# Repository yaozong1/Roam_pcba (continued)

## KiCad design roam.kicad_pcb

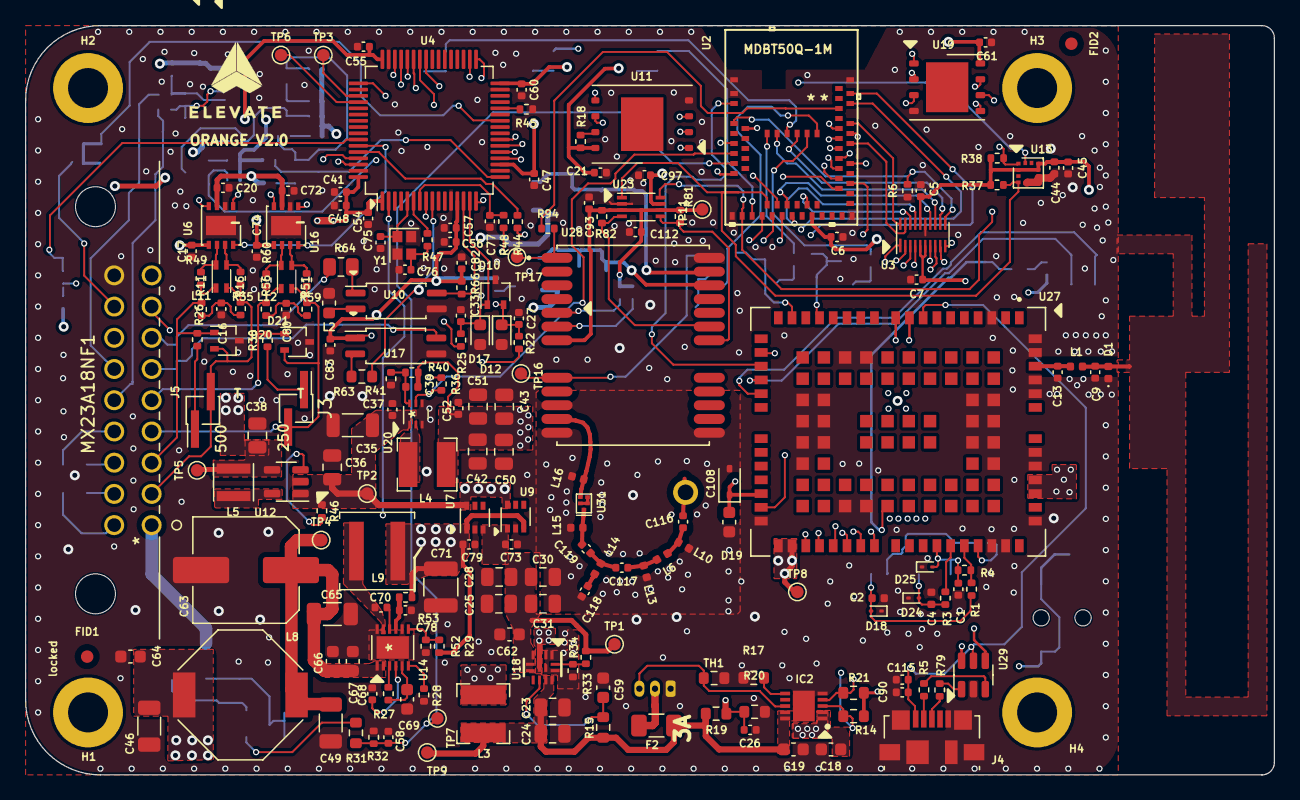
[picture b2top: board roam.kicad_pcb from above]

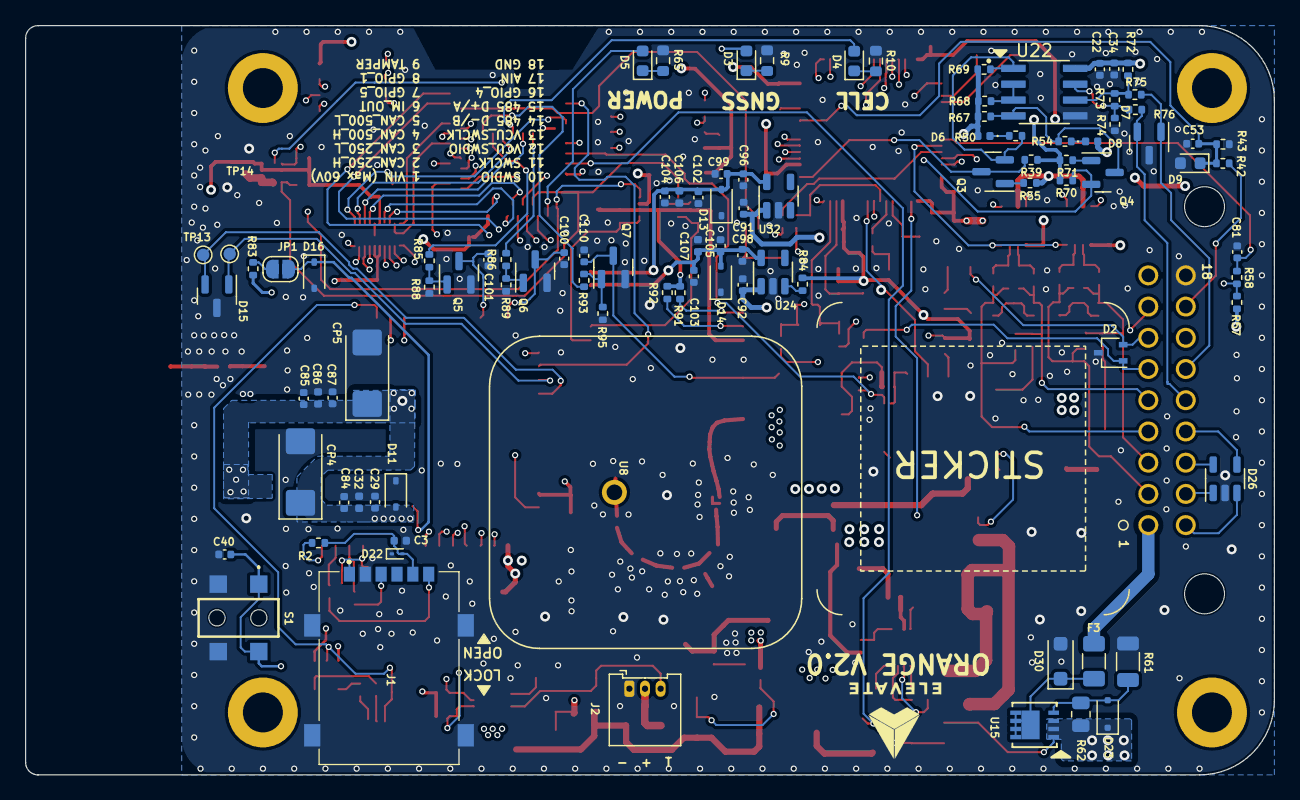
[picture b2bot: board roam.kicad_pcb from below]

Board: 6 copper layers, 100.0 x 60.0 mm, 301 parts (99 on the bottom side), 183 nets.

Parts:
C1, C5, C7, C17, C20, C21, C22, C26, C27, C29, C33, C37, C40, C44, C47, C48, C52, C53, C54, C55, C57, C58, C60, C61, C72, C73, C74, C77, C78, C79, C81, C82, C83, C85, C93, C97, C99, C104, C105, C110, C112, C115: 100nF; C_0402_1005Metric
C2, C3, C4, C32, C39, C86, C106, C107: 33pF; L_0402_1005Metric
C6, C41, C45, C102, C103: 10uF; C_0402_1005Metric
C9, C13: DNP; C_0402_1005Metric
C16, C80: 1nF; C_0402_1005Metric
C18, C19, C59, C62: 1uF; C_0603_1608Metric
C23, C24, C25, C28, C30, C31, C36, C38, C42, C43, C50, C51: 22uF; C_0805_2012Metric
C34, C56, C90, C96, C98: 1uF; C_0402_1005Metric
C35: 47uF; L_1206_3216Metric
C46, C49, C65: 4.7uF; C_1206_3216Metric
C63: 33uF; C_Elec_8x10.2
C64, C66: 0.1uF; C_0603_1608Metric
C67: 220pF; C_0603_1608Metric
C68: 12pF; C_0402_1005Metric
C69, C108: 2.2uF; C_0603_1608Metric
C70: 0.1uF; C_0402_1005Metric
C71: 22uF; C_1210_3225Metric
C75, C76, C84, C87: 10pF; C_0402_1005Metric
C91, C92: 2.2uF; C_0402_1005Metric
C100, C101: 10nF; C_0402_1005Metric
C116: 33nF; C_0402_1005Metric
C117, C118, C119: 4.7pF; C_0402_1005Metric
CP4, CP5: T520C107M010ATE025; CP_EIA-6032-28_Kemet-C
D1: AXGD10402; D_0402_1005Metric
D2, D10: BAT54AW; SOT-323_SC-70
D3, D4, D5: LED; LED_0603_1608Metric
D6, D8: LED; LED_0402_1005Metric
D7: PESD8V0L2BT-N; SOT-23
D9, D12, D17: 3v3; D_0603_1608Metric
D11, D13, D14: ESD56151W04; D_SOD-323
D15: PESD3V3L2BT; SOT-23
D16, D19: PESD3V3L1BA-N; D_SOD-323
D18, D22, D24, D25: ESD9C5.0ST5G; D_SOD-923
D20, D21: SM712_SOT23; SOT-323_SC-70
D23: MM3Z18VT1G; D_SOD-323F
D26: D5V0L4B5TS (5V); SOT-23-5
D30: SMF70CA (70V TVS); D_SOD-123F
F2: 3A; Fuse_1206_3216Metric
F3: 2A; Fuse_1206_3216Metric
FID1, FID2: Fiducial; Fiducial_1mm_Mask2mm
H1, H2, H3, H4: MountingHole; MountingHole_3.2mm_M3_DIN965_Pad
IC2: MCP73833T-FCI/MF; SON50P300X300X100-11N-D
J1: SIM8060-6-0-14-00-A; SIM8060601400A
J2: Battery; Molex_PicoBlade_53048-0310_1x03_P1.25mm_Horizontal
J3, J5: Conn_01x03_Pin; PinHeader_1x02_P1.27mm_Vertical_SMD_Pin1Left
J4: USB_B_Micro; USB_Micro-B_Molex_47346-0001
JP1: SolderJumper_2_Open; SolderJumper-2_P1.3mm_Open_RoundedPad1.0x1.5mm
L1, L6: 0nH; L_0402_1005Metric
L2: 2.2uH; L_0603_1608Metric
L3: 1.5uH; L_Bourns-SRN4018
L4: 2.2uH; L_Bourns-SRN4018
L5: 2.2uH; L_Taiyo-Yuden_MD-3030
L8: 10uH; L_Bourns-SRU1028_10.0x10.0mm
L9: 10uH; L_Coilcraft_XAL5030-XXX
L10, L13: DNP; L_0402_1005Metric
L11, L12: L_Ferrite_Coupled_1243; L_CommonModeChoke_Laird_CMA0805
L14: 9.1nH; L_0402_1005Metric
L15, L16: 5.1nH; L_0402_1005Metric
Q3, Q4: MMBT3904; SOT-23
Q5, Q6, Q7: BC846A,215; SOT-23
R1, R2, R3, R5, R35, R47, R49, R59, R60, R79, R94: 0; R_0402_1005Metric
R4: 15k; R_0402_1005Metric
R6, R42, R57: 100k; R_0402_1005Metric
R9, R10, R65: 750; R_0603_1608Metric
R11, R16, R51, R56: 2k8; R_0402_1005Metric
R14, R21: 4K7; R_0603_1608Metric
R15, R31: 300k; R_0603_1608Metric
R17: 2k; R_0603_1608Metric
R18, R46, R55, R58, R66, R71: 1k; R_0402_1005Metric
R19: 100k; R_0603_1608Metric
R20: 330k; R_0603_1608Metric
R22, R25: 2k; R_0402_1005Metric
R26, R30: 120; R_0402_1005Metric
R27, R32, R36, R39, R44, R45, R67, R68, R69, R70, R84: 10k; R_0402_1005Metric
R28, R73: DNP; R_0402_1005Metric
R29: 105k; R_0402_1005Metric
R33: 348k; R_0402_1005Metric
R34: 71.5k; R_0402_1005Metric
R37, R38, R72, R74, R85, R86, R93: 4K7; R_0402_1005Metric
R40: 169k; R_0402_1005Metric
R41: 30k; R_0402_1005Metric
R43: 3.3k; R_0402_1005Metric
R48: 100; R_0402_1005Metric
R50, R54: 5.1K; R_0402_1005Metric
R52: 23.2k; R_0402_1005Metric
R53: 4.7; R_0402_1005Metric
R61: 20k; R_1206_3216Metric
R62: 220k; R_0805_2012Metric
R63: 130; R_0603_1608Metric
R64: 680; R_0805_2012Metric
R75, R76: 10; R_0402_1005Metric
R81, R82: 2K2; R_0402_1005Metric
R83: 4k7; R_0402_1005Metric
R88, R89, R95: 47K; R_0402_1005Metric
R91, R92: 39k; R_0402_1005Metric
S1: ESE-11MV9; ESE11MV9
TCLOGO1, TCLOGO2: SYM_Magnet_Large; Logo-Text-Silk-Smaller
TCLOGO3: SYM_Magnet_Large; Sticker-frame
TCLOGO4: SYM_Magnet_Large; SIM-instruction
TH1: DNP; R_0603_1608Metric
TP1, TP2, TP4, TP5, TP8, TP11, TP16, TP17: TestPoint; TestPoint_Pad_D1.0mm
TP3: UART_TX; TestPoint_Pad_D1.0mm
TP6: UART_RX; TestPoint_Pad_D1.0mm
TP7: EBL; TestPoint_Pad_D1.0mm
TP9: T_BAT; TestPoint_Pad_D1.0mm
TP13: DBG_TX; TestPoint_Pad_D1.0mm
TP14: DBG_RXD; TestPoint_Pad_D1.0mm
U2: MDBT50Q-1M
U3: TXB0108DQSR; USON-20_2x4mm_P0.4mm
U4: STM32F105RBT6; LQFP-64_10x10mm_P0.5mm
U6, U16: MCP2562-E/MF; DFN-8-1EP_3x3mm_P0.65mm_EP1.55x2.4mm
U7, U9: LM66100DCKR; SOT-363_SC-70-6
U8: GP.1575.25.2.A.02
U10, U17: LTV-217; SOIC-4_4.55x2.6mm_P1.27mm
U11: W25N512GVEIG; WSON-8-1EP_8x6mm_P1.27mm_EP3.4x4.3mm
U12: LM3671MF-3.3/NOPB; SOT-23-5
U13: LIS2DH12TR; LIS12DH
U14: MAX17643ATC+; MAX17643ATCplus
U15: FDMC86139P; WDFN8-511DH-O_3p3x3p3x0p65_OSI
U18: MP3423GG; MP3423
U19: MX25R6435FZNIL0; WSON-8-1EP_6x5mm_P1.27mm_EP3.4x4mm
U20: TPS566242DRLR
U22: MAX13487EESAT; SOIC127P600X175-8N
U23: TXS0102DCU; VSSOP-8_2.3x2mm_P0.5mm
U24, U32: LP5907MFX-3.3; SOT-23-5
U27: EG915ULAAB-N05-SNNSA; XCVR_EG915ULAAB-N05-SNNSA
U28: LC29H; XCVR_LC29H
U29: USBLC6-2SC6; SOT-23-6
U31: B39162B8389P810; GNSS_Fliter 1.4x1.1mm
Y1: 25MHz; Crystal_SMD_2016-4Pin_2.0x1.6mm
locked: MX23A18NF1

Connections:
1V8: C7.1, C108.1, D19.1 (A1), R83.2, U3.5 (VCCA), U3.6 (OE), U27.29 (VDD_EXT)
2V8: C93.1, C112.2, R81.1, R82.1, R91.2, R92.2, TP11.1, U23.3 (VCCA), U23.6 (OE), U28.7 (VDD_EXT)
3V3_ALWAYS_ON: C5.1, C6.1, C17.2, C21.1, C38.1, C41.1, C44.1, C45.1, C47.2, C48.2, C54.2, C55.2, C56.1, C57.2, C60.2, C61.1, C74.2, C82.1, C83.1, C97.1, L5.2, R14.2, R18.1, R21.2, R36.1, R37.1, R38.1, R39.2, R57.2, R66.1, R70.2, R71.2, R84.2, TP5.1, U2.28 (VDD), U3.16 (VCCB), U4.1 (VBAT), U4.13 (VDDA), U4.19 (VDD), U4.32 (VDD), U4.48 (VDD), U4.64 (VDD), U6.5 (Vio), U11.8 (VCC), U12.4 (FB), U13.2 (CS), U13.9 (VDD), U13.10 (VDD_IO), U16.5 (Vio), U17.1, U19.8 (VCC), U23.7 (VCCB)
4V0: C29.1, C32.1, C39.1, C42.1, C43.1, C50.1, C51.1, C52.1, C84.2, C85.1, C86.1, C87.2, CP4.1, CP5.1, D11.2 (A2), L4.2, R40.1, TP8.1, U27.32 (VBAT_BB), U27.33 (VBAT_BB), U27.52 (VBAT_RF), U27.53 (VBAT_RF)
4V7_BOOST: C25.1, C28.1, C30.1, C31.1, C62.1, C73.1, R33.2, TP1.1, U7.3 (~CE), U9.1 (VIN), U18.4 (OUT), U18.5 (OUT), U18.6 (OUT)
5V0: C20.2, C22.1, C34.1, C35.1, C36.1, C37.1, C72.2, C91.1, C92.1, D6.2 (A), D8.2 (A), R46.1, R55.2, R67.2, R68.2, R69.2, R72.2, TP2.1, U6.3 (VDD), U7.6 (VOUT), U9.6 (VOUT), U12.1 (VIN), U16.3 (VDD), U20.1 (VIN), U22.8 (VCC), U24.1 (IN), U32.1 (IN)
5V0_BUCK: C18.1, C71.1, C79.1, IC2.1 (VDD_1), IC2.2 (VDD_2), L9.1, R29.1, R53.2, U7.1 (VIN), U9.3 (~CE)
60VIN: C49.1, C63.1, C65.1, C66.1, C67.1, L8.2, TP4.1, U14.1 (VIN), U14.2 (EN/UVLO)
+60V_IN: F3.1, locked.1
/100V_AIN: C53.1, D9.1 (K), R42.2, R43.1, U4.26 (PB0)
/3423_SW: L3.2, U18.3 (SW), U18.14 (SW)
/ACC_INT: U2.8 (P1.15), U13.12 (INT_1)
/AIN_100V: R42.1, locked.17
/AUX_LED: D5.2 (A), U2.17 (P0.00/XL1)
/CAN_250_H: D20.2 (A2), J5.2, L11.2, R16.1, R35.1, locked.2
/CAN_250_L: D20.1 (A1), L11.3, R11.2, R26.2, R49.1, locked.3
/CAN_500_H: D21.2 (A2), J3.2, L12.2, R51.1, R59.1, locked.4
/CAN_500_L: D21.1 (A1), L12.3, R30.2, R56.2, R60.1, locked.5
/CAN_SHDN: U4.59 (PB7), U6.8 (SHDN), U16.8 (SHDN)
/CHARGER_STAT_1: IC2.3 (STAT1), R14.1, U2.38 (P0.16)
/CHARGER_STAT_2: IC2.4 (STAT2), R21.1, U2.41 (P0.17)
/CONN_LED: D4.2 (A), U2.58 (P1.07)
/CTS_1V8: U3.4 (A4), U27.36 (MAIN_CTS)
/CTS_3V3: U2.24 (P0.08), U3.17 (B4)
/D+/A: D7.1 (A1), R75.1, locked.15
/D-/B: D7.2 (A2), R76.1, locked.14
/DCD_1V8: U3.7 (A5), U27.38 (MAIN_DCD)
/DCD_3V3: U2.23 (P0.07), U3.14 (B5)
/EBL: C58.1, R31.2, R32.1, TP7.1, U2.12 (P0.31/AIN7)
/EBL_60V: C46.1, C64.1, D23.1 (K), L8.1, R31.1, R62.1, U15.1 (S), U15.2 (S), U15.3 (S)
/FLASH_CS: U2.40 (P0.18/RST/QSPI-CSN), U19.1 (CS#)
/FLASH_MISO: U2.43 (P0.21/QSPI), U19.2 (SO/SIO1)
/FLASH_MISO2: U2.46 (P0.22/QSPI), U19.3 (WP#/SIO2)
/FLASH_MISO3: U2.45 (P0.23/QSPI), U19.7 (RST#/SIO3)
/FLASH_MOSI: U2.47 (P1.00/QSPI), U19.5 (SI/SIO0)
/FLASH_SCK: U2.42 (P0.19/QSPI-SCK), U19.6 (SCLK)
/GNSS_ANT: L16.2, U28.11 (RF_IN), U31.4 (OUT)
/GPIO15: R84.1, U24.3 (EN)
/GPIO_1: R22.1, locked.8
/GPIO_3V3_1: C27.1, D10.2, D12.1 (K), R22.2, U4.8 (PC0)
/GPIO_3V3_4: C33.1, D10.1, D17.1 (K), R25.2, U4.15 (PA1)
/GPIO_3V3_5: R66.2, U4.14 (PA0), U10.4
/GPIO_4: R25.1, locked.16
/GPIO_5: D2.2, R64.1, locked.7
/HSE_OSC_1: C75.1, U4.5 (PD0), Y1.1
/HSE_OSC_2: R47.1, U4.6 (PD1)
/IBL: C26.1, R19.2, R20.1, U2.14 (P0.30/AIN6)
/IM_OUT: D2.1, U17.4, locked.6
/IM_OUT_3V3: R63.1, U4.9 (PC1)
/LC29_RESET: C110.2, Q7.3 (C), TP16.1, U28.8 (~RESET)
/LC29_RESET_ESP32: R93.2, U2.61 (P1.01)
/LC29_WUP: R94.2, TP17.1, U28.1 (WAKEUP)
/LC29_WUP_ESP32: R94.1, U2.50 (P1.02)
/MODEM_DTR_1V8: U3.9 (A7), U27.30 (MAIN_DTR)
/MODEM_DTR_3V3: U2.59 (P1.05), U3.12 (B7)
/MODEM_RI_1V8: U3.8 (A6), U27.39 (MAIN_RI)
/MODEM_RI_3V3: U2.57 (P1.06), U3.13 (B6)
/MODEM_RX_1V8: U3.1 (A1), U27.34 (MAIN_RXD)
/MODEM_RX_3V3: U2.48 (P0.24), U3.20 (B1)
/MODEM_TX_1V8: U3.2 (A2), U27.35 (MAIN_TXD)
/MODEM_TX_3V3: U2.44 (P0.20), U3.19 (B2)
/NET_LED: U2.3 (P1.10), U27.21 (NET_STATUS)
/NRESET: R86.2, U2.56 (P1.04)
/NRF_LED: D3.2 (A), U2.5 (P1.12)
/NTC: IC2.8 (THERM), J2.3, TH1.1
/PWRKEY: R85.2, U2.60 (P1.03)
/RF_ANT: C13.1, L1.1, U27.60 (ANT_MAIN)
/RS485_RX: Q4.2 (E), R70.1, U4.16 (PA2)
/RS485_TX: Q3.3 (C), R39.1, U4.17 (PA3)
/RTS_1V8: U3.3 (A3), U27.37 (MAIN_RTS)
/RTS_3V3: U2.27 (P0.11), U3.18 (B3)
/SCL: R38.2, U2.16 (P0.27), U13.1 (SCL/SPC), U23.8 (B1)
/SCL_LC29: R82.2, U23.4 (A2), U28.19 (I2C_SCL)
/SDA: R37.2, U2.19 (P0.26), U13.4 (SDA/SDI/SDO), U23.1 (B2)
/SDA_LC29: R81.2, U23.5 (A1), U28.18 (I2C_SDA)
/SIM_CHIP_CLK: C3.1, D22.2 (A2), J1.C3 (CLK), R2.2
/SIM_CHIP_DATA: C2.1, D18.2 (A2), J1.C7 (I/O), R1.2
/SIM_CHIP_RST: C4.1, D24.2 (A2), J1.C2 (RST), R3.2
/SIM_CLK: R2.1, U27.46 (USIM1_CLK)
/SIM_DATA: R1.1, R4.1, U27.45 (USIM1_DATA)
/SIM_RST: R3.1, U27.44 (USIM1_RST)
/SIM_VDD: C1.1, D25.2 (A2), J1.C1 (VCC), R4.2, U27.43 (USIM1_VDD)
/STATUS_LED: U3.10 (A8), U27.20 (STATUS)
/STATUS_LED_3V3: R6.2, U2.4 (P1.11), U3.11 (B8)
/SWDCLK: D26.1 (K), U2.53 (SWDCLK), locked.11
/SWDIO: D26.3 (K), U2.51 (SWDIO), locked.10
/TAMPER_CONN: R57.1, R58.2, locked.9
/U20_EN: R36.2, U2.10 (P0.29/AIN5), U20.5 (EN)
/UART_RS485_RX_5V: Q4.3 (C), R54.2, R67.1, U22.4 (DI)
/UART_RS485_TX_5V: Q3.2 (E), R50.2, R69.1, U22.1 (RO)
/USB+: U27.9 (USB_DP), U29.6 (I/O1)
/USB-: U27.10 (USB_DM), U29.4 (I/O2)
/USB_DM: R5.2, U29.3 (I/O2)
/USB_DP: R79.2, U29.1 (I/O1)
/USB_VBUS: C90.1, C115.1, J4.1 (VBUS), U27.8 (USB_VBUS), U29.5 (VBUS)
/VCU_BOOT0: R44.2, U2.36 (P0.14)
/VCU_CAN1_RX: U4.61 (PB8), U16.4 (RXD)
/VCU_CAN1_TX: U4.62 (PB9), U16.1 (TXD)
/VCU_CAN2_RX: U4.33 (PB12), U6.4 (RXD)
/VCU_CAN2_TX: U4.34 (PB13), U6.1 (TXD)
/VCU_FLASH_CS: U4.20 (PA4), U11.1 (CS#)
/VCU_FLASH_MISO: U4.22 (PA6), U11.2 (SO/SIO1)
/VCU_FLASH_MOSI: U4.23 (PA7), U11.5 (SI/SIO0)
/VCU_FLASH_SCK: U4.21 (PA5), U11.6 (SCLK)
/VCU_FLASH_WP: U4.41 (PA8), U11.3 (WP#/SIO2)
/VCU_NRST: R48.2, U2.37 (P0.13)
/VCU_SWCLK: D26.4 (K), U4.49 (PA14), locked.13
/VCU_SWDIO: D26.5 (K), U4.46 (PA13), locked.12
/VCU_TAMP: C40.1, S1.1 (NO_1), S1.2 (NO_2), U4.2 (PC13)
/VCU_TAMPER_CONN: C81.1, R58.1, U4.58 (PB6)
/VCU_USART2_CTS: U2.20 (P0.04/AIN2), U4.44 (PA11)
/VCU_USART2_RTS: U2.18 (P0.01/XL2), U4.45 (PA12)
/VCU_USART2_RX: U2.21 (P0.05/AIN3), U4.43 (PA10)
/VCU_USART2_TX: U2.22 (P0.06), U4.42 (PA9)
/usb_boot: D16.1 (A1), JP1.1 (A), U27.75 (USB_BOOT)
GND: C1.2, C2.2, C3.2, C4.2, C5.2, C6.2, C7.2, C9.1, C9.2, C13.2, C16.2, C17.1, C18.2, C19.2, C20.1, C21.2, C22.2, C23.2, C24.2, C25.2, C26.2, C27.2, C28.2, C29.2, C30.2, C31.2, C32.2, C33.2, C34.2, C35.2, C36.2, C37.2, C38.2, C40.2, C41.2, C42.2, C43.2, C44.2, C45.2, C46.2, C47.1, C48.1, C49.2, C50.2, C51.2, C52.2, C53.2, C54.1, C55.1, C56.2, C57.1, C58.2, C59.2, C60.1, C61.2, C62.2, C63.2, C64.2, C65.2, C66.2, C67.2, C68.2, C69.2, C71.2, C72.1, C73.2, C74.1, C75.2, C76.2, C77.1, C78.2, C79.2, C80.2, C81.2, C82.2, C83.2, C84.1, C85.2, C86.2, C87.1, C90.2, C91.2, C92.2, C93.2, C96.2, C97.2, C98.2, C99.2, C100.1, C101.1, C102.2, C103.2, C104.1, C105.1, C106.2, C107.2, C108.2, C110.1, C112.1, C115.2, C118.1, CP4.2, CP5.2, D1.1 (A1), D1.2 (A2), D2.3, D7.3 (A3), D9.2 (A), D10.3, D11.1 (A1), D12.2 (A), D13.1 (A1), D14.1 (A1), D15.3 (common), D16.2 (A2), D17.2 (A), D18.1 (A1), D19.2 (A2), D20.3 (common), D21.3 (common), D22.1 (A1), D24.1 (A1), D25.1 (A1), D26.2 (A), D30.2 (A2), IC2.5 (VSS), IC2.11 (EP), J1.C5 (GND_1), J1.G1 (GND_2), J1.G2 (GND_3), J1.G3 (GND_4), J1.G4 (GND_5), J2.1, J4.5 (GND), J4.6 (Shield), L1.2, L2.2, L10.1, L13.1, L15.1, L16.1, Q5.2 (E), Q6.2 (E), Q7.2 (E), R6.1, R9.1, R10.1, R17.2, R20.2, R28.1, R32.2, R34.1, R41.2, R43.2, R45.1, R52.2, R61.2, R65.1, R74.1, R88.1, R89.1, R95.1, S1.C1 (COM_1), S1.C2 (COM_2), TH1.2, U2.1 (GND), U2.2 (GND), U2.15 (GND), U2.33 (GND), U2.55 (GND), U3.15 (GND), U4.12 (VSSA), U4.18 (VSS), U4.31 (VSS), U4.47 (VSS), U4.63 (VSS), U6.2 (VSS), U6.9 (PAD), U7.2 (GND), U9.2 (GND), U10.3, U11.4 (GND), U12.2 (GND), U13.5 (RES), U13.6 (GND), U13.7 (GND), U13.8 (GND), U14.8 (GND), U14.12 (PGND), U14.13 (EPAD), U16.2 (VSS), U16.9 (PAD), U17.3, U18.1 (PGND), U18.2 (PGND), U18.11 (AGND), U18.13 (PGND), U19.4 (GND), U20.3 (AGND), U20.4 (GND), U22.5 (GND), U23.2 (GND), U24.2 (GND), U27.3 (GND), U27.31 (GND), U27.47 (USIM1_GND), U27.48 (GND), U27.50 (GND), U27.54 (GND), U27.55 (GND), U27.58 (GND), U27.59 (GND), U27.61 (GND), U27.62 (GND), U27.67 (GND), U27.68 (GND), U27.69 (GND), U27.70 (GND), U27.71 (GND), U27.72 (GND), U27.73 (GND), U27.74 (GND), U27.79 (GND), U27.80 (GND), U27.81 (GND), U27.82 (GND), U27.89 (GND), U27.90 (GND), U27.91 (GND), U27.100 (GND), U27.101 (GND), U27.102 (GND), U28.10 (GND), U28.12 (GND), U28.13 (GND), U28.24 (GND), U29.2 (GND), U31.2 (GND), U31.3 (GND), U31.5 (GND), U32.2 (GND), Y1.2, Y1.4, locked.18
unnamed: C16.1, R11.1, R16.2
unnamed: C76.1, R47.2, Y1.3
unnamed: C80.1, R51.2, R56.1
unnamed: C116.1, L6.1, L10.2
unnamed: C116.2, U8.1
unnamed: C117.1, L6.2, L13.2
unnamed: C117.2, C119.1, L14.2
unnamed: C118.2, L14.1
unnamed: D3.1 (K), R9.2
unnamed: D4.1 (K), R10.2
unnamed: D5.1 (K), R65.2
unnamed: D6.1 (K), R50.1
unnamed: D8.1 (K), R54.1
unnamed: D15.1 (A1), TP14.1, U27.22 (DBG_RXD)
unnamed: D15.2 (A2), TP13.1, U27.23 (DBG_TXD)
unnamed: D23.2 (A), R61.1, R62.2, U15.4 (G)
unnamed: D30.1 (A1), F3.2, U15.5 (D), U15.6 (D), U15.7 (D), U15.8 (D)
unnamed: IC2.6 (PROG), R17.1
unnamed: F2.2, J2.2
unnamed: J3.1, R30.1
unnamed: J4.3 (D+), R79.1
unnamed: J4.2 (D-), R5.1
unnamed: J5.1, R26.1
unnamed: JP1.2 (B), R83.1
unnamed: L2.1, U10.2
unnamed: Q3.1 (B), R55.1
unnamed: Q4.1 (B), R71.1
unnamed: Q5.1 (B), R85.1, R88.2
unnamed: C101.2, Q5.3 (C), U27.15 (PWRKEY)
unnamed: Q6.1 (B), R86.1, R89.2
unnamed: C100.2, Q6.3 (C), U27.17 (~RESET)
unnamed: Q7.1 (B), R93.1, R95.2
unnamed: R63.2, U17.2
unnamed: R64.2, U10.1
unnamed: R44.1, U4.60 (BOOT0)
unnamed: C77.2, R48.1, U4.7 (NRST)
unnamed: R45.2, U4.28 (PB2)
unnamed: TP3.1, U4.51 (PC10)
unnamed: TP6.1, U4.52 (PC11)
unnamed: L11.1, R35.2, U6.7 (CANH)
unnamed: L11.4, R49.2, U6.6 (CANL)
unnamed: R18.2, U11.7 (RST#/SIO3)
unnamed: R46.2, U12.3 (EN)
unnamed: L5.1, U12.5 (SW)
unnamed: R27.2, U14.3 (*RESET)
unnamed: C70.2, U14.10 (BST)
unnamed: C78.1, R53.1, U14.9 (EXTVCC)
unnamed: R29.2, R52.1, U14.7 (FB)
unnamed: C70.1, L9.2, U14.11 (LX)
unnamed: R28.2, U14.6 (RT/SYNC)
unnamed: C68.1, U14.4 (SS)
unnamed: C69.1, R27.1, U14.5 (VCC)
unnamed: L12.1, R59.2, U16.7 (CANH)
unnamed: L12.4, R60.2, U16.6 (CANL)
unnamed: C59.1, R15.2, U18.8 (EN)
unnamed: R33.1, R34.2, U18.12 (FB)
unnamed: C39.2, R40.2, R41.1, U20.6 (FB)
unnamed: L4.1, U20.2 (SW)
unnamed: R72.1, R73.2, R75.2, U22.6 (A)
unnamed: R73.1, R74.2, R76.2, U22.7 (B)
unnamed: R68.1, U22.2 (~RE), U22.3 (~SHDN)
unnamed: R91.1, U28.5 (D_SEL1)
unnamed: R92.1, U28.6 (D_SEL2)
unnamed: C119.2, L15.2, U31.1 (IN)
VBAT: C19.1, C23.1, C24.1, F2.1, IC2.9 (VBAT_1), IC2.10 (VBAT_2), L3.1, R15.1, R19.1, TP9.1, U18.9 (IN), U18.10 (INA)
VCC_LC29: C96.1, C99.1, C102.1, C104.2, C106.1, D13.2 (A2), U28.23 (VCC), U32.5 (OUT)
V_BCKP_LC29: C98.1, C103.1, C105.2, C107.1, D14.2 (A2), U24.5 (OUT), U28.22 (V_BCKP)

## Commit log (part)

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2022-12-15 add README
2022-12-15 Init
2022-12-15 Placed sketch components
2022-12-20 Reduced component count
2022-12-21 Updated smaller footprint
2022-12-26 Worked on connector
2022-12-28 Draw 95V
2022-12-28 added 3d models for missing parts
2022-12-29 Added DC booster
2022-12-29 new dc booster
2022-12-29 Save
2022-12-30 Routing
2023-01-02 Routed
2023-01-02 Component selection in progress
2023-01-05 Added Digi-key PN to all components
2023-01-23 phase 2 start
2023-01-26 single shield on vin dcdc
2023-01-31 updated layout, not done
2023-01-31 Done, execpt ERC
2023-02-01 ready for production
2023-02-01 changed tvs diodes and added missing cupper fill
2023-02-02 gerber sent to production
2023-02-08 gsm antenna template
2023-02-09 tc-kicad-comp folder
2023-02-15 new rounting 2/15
2023-02-17 before updating to kicad7
2023-02-19 KICAD 7
2023-02-21 P3_ ready to print
2023-02-21 fix silkscreen
2023-02-21 Added all 3d models
2023-02-22 Fixed In1 and In2 Sequence
2023-02-23 started to implement the changelog for phase 3
2023-03-08 new 5V dcdc
2023-03-09 save before mayhem
2023-03-09 unboken gnd plane + cleared space around the LNA
2023-03-10 Almost ready for prod, Need some cleanup
2023-03-14 added the rest of the vcu pins + input prot + small fixes everywhere
2023-03-15 Ready for review
2023-03-16 fixed some errors
2023-03-16 fixed some wrong MPNs
2023-03-16 P4 sent to prod for GBG
2023-03-17 updated antenna and production
2023-04-25 schematic cleanup, added missing decaps in can section
2023-05-30 component placment and routing iterated, new VCU
2023-05-30 some cleanup
2023-05-31 ready for print
2023-06-07 p5_sz
2023-06-13 Moved charger STATs to 3V3 rail and CAN VCC to 5V rail
2023-06-14 phase-2 update, changed to horizontal bat connector
2023-06-16 fixed unconnected GND
2023-06-16 Added 3 testing point UART for jig
2023-06-16 Fixed flash footprint to WSON 6*8MM
2023-06-19 Fixed the rescue layer issue
2023-07-06 Fullfill the info for all components
2023-08-03 reday to produce
2023-08-03 Fixed production issue
2023-08-22 Changed TVS D30 TO Bi-directional
2023-08-24 p7 ready
2023-08-24 xxxx
2023-08-24 Sent
2023-09-13 Update production info
2023-09-18 rm leds, added trace for u20
2023-09-18 Added a jumper for CAN termination and updated mpns for status LEDs
2023-09-22 clean up
2023-09-25 Rerouted UART2 to UART1, changed pin on CAN1
2023-09-26 drc, ready for review
2023-11-02 some cleanup and new comments on the schematic
2023-11-07 revision for production
2023-11-08 update bom
2023-11-08 bom update
2023-11-08 LOGO update
2023-12-04 optimized the assembly instrction for ryder
2023-12-08 added D12 13 16 17 PIN1 MARK
2023-12-21 Added LC79H
2023-12-29 12/29
2023-12-29 sch update
2024-01-19 saving
2024-01-22 1/22
2024-01-26 fix the bom
2024-01-29 update components
2024-02-06 Added ESD for 1v8 & DBG_UART
2024-02-06 Added esd diode for sim, usb
2024-02-06 quectel review done
2024-02-28 the first commit for nrf_quectel
2024-03-09 added filter for gnss
2024-03-10 saved
2024-03-10 updated lib
2024-03-10 saved 3/10
2024-03-10 saved 3/10 date
2024-03-14 3/14 saved
2024-03-14 done for review
2024-03-21 clean and move
2024-03-25 updated the logo
2024-03-26 nrf flash done
2024-04-01 saved 4/1
2024-04-03 done
2024-04-12 updated 4/12
2024-04-19 stripped down schematic and started on pcb layout
2024-05-08 saved 5/8
2024-05-16 Printed
2024-08-21 8/21
2024-08-21 compact_Verision for review
2024-09-02 struggle with tons of drc issues
2024-09-03 fixed missed mpn
2024-09-09 changed modem eg915 -> eg916
2024-09-10 new modem, before routing
2024-09-10 middle of routing savepoint
2024-09-10 saved route progress 80%
2024-09-23 Added gnss power
2024-09-23 ready to order
2024-09-24 update bom info
2024-11-08 save 11/9
2024-11-14 done before delete nrf
2024-11-20 done before delete the old stuff
2024-11-26 done before gnd optimization
2024-12-07 printed on JLC
2025-03-13 added charge_enable
2025-03-13 added the level shifter for rs485
2025-03-13 changed GNSS level shifter to TXB0104PW(BIGGER)
2025-03-13 added test point for gnss uart
2025-03-13 start layout
2025-03-13 changed TXB0104RU BACJ
2025-03-13 changed
2025-03-18 lite v3 done
2025-03-25 added EG800K
2025-03-25 added LDO
2025-03-26 ‘saved’
2025-03-29 almost done
2025-03-31 saved 3d models
2025-04-01 RIGHT BEFORE SMT
2025-04-07 updated bom info based on JLC
2025-04-07 updated bom
2025-04-08 done smt
2025-04-23 update bom -
2025-04-30 save bom
2025-04-30 save bom2
2025-07-04 edge_e42c done
2025-08-06 print for Roam
2025-08-06 update the bom
2025-08-06 WITH DNP
2025-08-06 full function
2025-12-29 xl v1.1
2025-12-29 update connector
2025-12-30 production
2025-12-30 dnp c117
2026-01-05 DFM update
